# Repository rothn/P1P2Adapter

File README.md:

# Interface PCB for HomeBus®-based Devices

Ever wonder what A/C systems talk about? Have a HomeBus®-based system like P1P2? Satisfy your curiosity and reward yourself with a fun and challenging project! Build or send away for one of these from your favorite PCB manufacturer, and enjoy direct access to your system. The possibilities are vast!

## Key Features
- Read from and optionally write to your HomeBus® (i.e., the stream of data running between parts of your A/C system and/or other HomeBus®-based devices)
- Power an Arduino Uno and companion devices (e.g., ESP8266) directly from your pre-existing wiring (i.e., the two wires coming out of the wall and going into the thermostat) instead of spending time on complicated power management features for battery operation
- Enjoy fully-specified KiCad files and an MIT license, empowering you to tweak or integrate this design into your own projects

## Specs and Validation
Based on reference design from MAX22088 datasheet, which is optimized for 57.6kbps. Observed to operate correctly on a system running at 9600bps over multi-hour burn-in test.

# Usage

## Warning
Using this device may damage your HomeBus® system! Check with your doctor to see if Tinkering is right for you. In my experiments, I tested everything the best that I could before using it and I suggest that you do the same. Also, note that this involves connection to AC wiring (the HomeBus®). Be careful with that step, as it can be dangerous.

## PCB Creation / Sourcing

### PCB Manufacturer
As of 2021, I paid $5 for 5 boards plus $15 for shipping from PCBWay, and at least one tested OK.

1. Export gerber files from KiCad and send them to your PCB manufacturer. Most have specific requirements for options in the export process. For PCBWay, find these [here](https://www.pcbway.com/blog/help_center/Generate_Gerber_file_from_Kicad_5_1_6.html).
2. Upload the zip file and select the correct tolerances on your PCB manufacturer's website. See the "design rules" menu in KiCad for these. Be sure to run a design rules check in the PCB editor just to double-check that you have the right options. Also be sure to select the correct number of vias, etc. The automated system is likely to catch errors, but getting things wrong here might slow down the process and affect your quoted price.
3. For anything not in the design rules, I highly recommend selecting the cheapest option.

Note: Most manufacturers can also populate the board with components, but this will be an extra cost. DIY'ing it can be fun and cheaper with the proper tools (hot air tool, soldering iron with small tip). Your manufacturer of choice will likely have this option on their website.

### At-Home (Guidelines)
There are people who are experts at this. Refer to their advice (Google around). Take the suggestions below with a grain of salt, but above all else, please keep in mind the inherent danger of working with chemicals at home:

The PCB can be manufactured with an at-home process by printing onto high-quality acetate compatible with your printer, UV exposure onto a presensitized, double-sided PCB, development, and etching. Toner transfer is unlikely to work due to the tolerances involved. CNC milling is also an option.

## Connection to Arduino Uno

### Software
I recommend the [P1P2Serial](https://github.com/Arnold-n/P1P2Serial) Arduino-compatible C++ library to interact with the HomeBus®. The included P1P2Serial library is a great interface tool. The P1P2 monitor example may be a helpful starting point for its ability to dump out packets from the bus as raw hex to the Arduino's USB serial device. Keep in mind that the decoding logic may not make sense for your specific device.

### Hardware
My test configuration is as follows. To allow writing to the bus, drive the RST pin on the interface board to GND instead of +5V.

- Connect J2 to Positive (sometimes called P1) and J3 to Neutral (sometimes called P2) on the HomeBus®. These are likely interchangeable, but I have not validated this in practice. See termination section of schematic (bottom-left).
- +12V -> Arduino Vin
- +5V -> 1k resistor -> interface board RST (this disables output, move input to GND to enable)
- GND -> Arduino GND
- VLOGIC -> Arduino +5V
- DOUT -> Arduino8* ||** (20kOhm resistor -> Arduino GND)
- DIN -> NC***

\*: Arduino labeled input "8" in "Digital PWM" section (Port B, Input 0 of ATmega328p)\
\*\*: Shorthand notation for "in parallel with"\
\*\*\*: Shorthand for "no connect" -- the data input is not connected to anything since writing to the bus is disabled

Notes (__Important__)
- The maximum load on +12V is 200mA, per the MAX22088 spec
- Do not use +5V for anything that draws more than 70 milliamps, and do not use it at all for external loads if using +12V
- I have found +12V outputs a very noisy 12V DC in my particular application, but the spec says that 7.3V is typical, without listing a maximum.

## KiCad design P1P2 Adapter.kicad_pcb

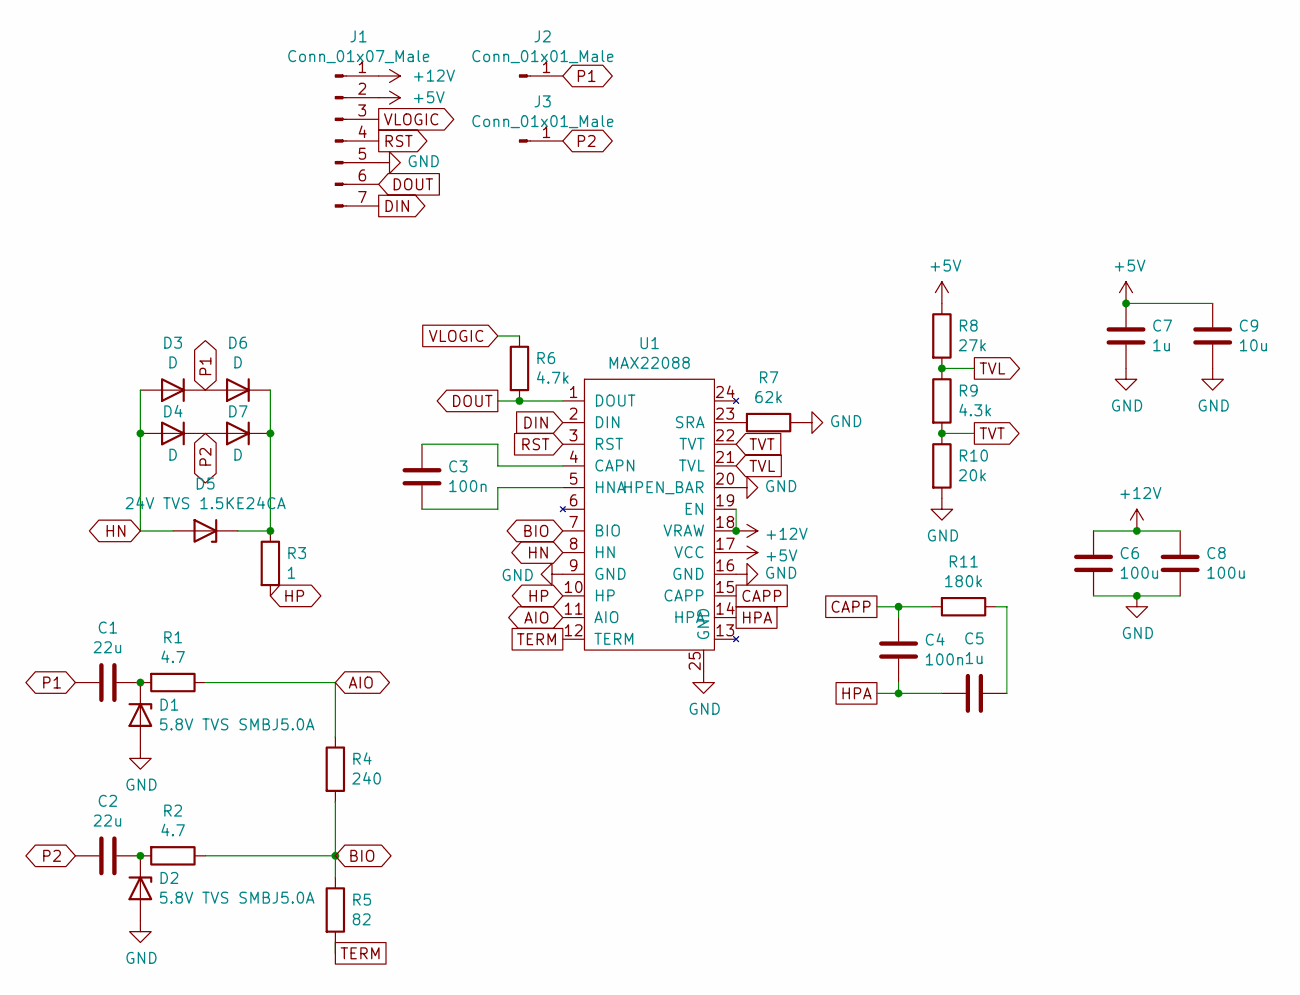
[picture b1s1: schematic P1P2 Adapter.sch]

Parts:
C1, C2: 22u; C_1206_3216Metric_Pad1.33x1.80mm_HandSolder
C3, C4: 100n; C_1206_3216Metric_Pad1.33x1.80mm_HandSolder
C5, C7: 1u; C_1206_3216Metric_Pad1.33x1.80mm_HandSolder
C6, C8: 100u; C_1206_3216Metric_Pad1.33x1.80mm_HandSolder
C9: 10u; C_1206_3216Metric_Pad1.33x1.80mm_HandSolder
D1, D2: 5.8V TVS SMBJ5.0A; D_SMB_Handsoldering
D3, D4, D6, D7: D; D_P600_R-6_P12.70mm_Horizontal
D5: 24V TVS 1.5KE24CA; D_DO-201_P12.70mm_Horizontal
J1: Conn_01x07_Male; PinHeader_1x07_P2.54mm_Vertical
J2, J3: Conn_01x01_Male; PinHeader_1x01_P2.54mm_Vertical
R1, R2: 4.7; R_1206_3216Metric_Pad1.30x1.75mm_HandSolder
R3: 1; R_1206_3216Metric_Pad1.30x1.75mm_HandSolder
R4: 240; R_1206_3216Metric_Pad1.30x1.75mm_HandSolder
R5: 82; R_1206_3216Metric_Pad1.30x1.75mm_HandSolder
R6: 4.7k; R_1206_3216Metric_Pad1.30x1.75mm_HandSolder
R7: 62k; R_1206_3216Metric_Pad1.30x1.75mm_HandSolder
R8: 27k; R_1206_3216Metric_Pad1.30x1.75mm_HandSolder
R9: 4.3k; R_1206_3216Metric_Pad1.30x1.75mm_HandSolder
R10: 20k; R_1206_3216Metric_Pad1.30x1.75mm_HandSolder
R11: 180k; R_1206_3216Metric_Pad1.30x1.75mm_HandSolder
U1: MAX22088; TQFN-24-1EP_4x4mm_P0.5mm_EP2.8x2.8mm_PullBack

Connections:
+5V: C7.1, C9.1, J1.2, R8.1, U1.17 (VCC)
+12V: C6.1, C8.1, J1.1, U1.18 (VRAW), U1.19 (EN)
AIO: R1.1, R4.1, U1.11 (AIO)
BIO: R2.1, R4.2, R5.1, U1.7 (BIO)
CAPP: C4.1, R11.2, U1.15 (CAPP)
DIN: J1.7, U1.2 (DIN)
DOUT: J1.6, R6.2, U1.1 (DOUT)
GND: C6.2, C7.2, C8.2, C9.2, D1.2 (A), D2.2 (A), J1.5, R7.1, R10.2, U1.9 (GND), U1.16 (GND), U1.20 (HPEN_BAR), U1.25 (GND)
HN: D3.2 (A), D4.2 (A), D5.2 (A), U1.8 (HN)
HP: R3.2, U1.10 (HP)
HPA: C4.2, C5.2, U1.14 (HPA)
unnamed: C1.2, D1.1 (K), R1.2
unnamed: C2.2, D2.1 (K), R2.2
unnamed: C3.1, U1.4 (CAPN)
unnamed: C3.2, U1.5 (HNA)
unnamed: C5.1, R11.1
unnamed: D5.1 (K), D6.1 (K), D7.1 (K), R3.1
unnamed: R7.2, U1.23 (SRA)
P1: C1.1, D3.1 (K), D6.2 (A), J2.1
P2: C2.1, D4.1 (K), D7.2 (A), J3.1
RST: J1.4, U1.3 (RST)
TERM: R5.2, U1.12 (TERM)
TVL: R8.2, R9.1, U1.21 (TVL)
TVT: R9.2, R10.1, U1.22 (TVT)
VLOGIC: J1.3, R6.1

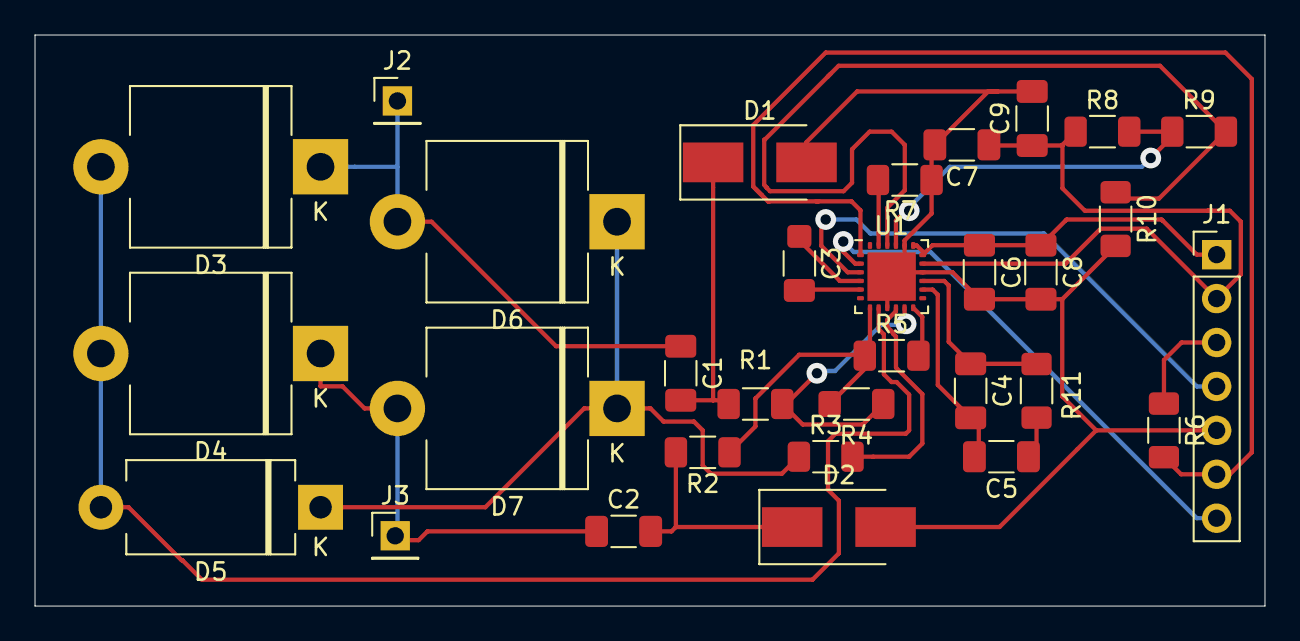
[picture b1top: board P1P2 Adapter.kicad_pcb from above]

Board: 2 copper layers, 71.1 x 33.0 mm, 31 parts (0 on the bottom side), 25 nets.

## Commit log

2021-09-15 Updated ground plane and PCB design
2021-11-28 Final touches, incl. design rule checks before having the board manufactured
2021-11-30 Fixed incorrect trim resistors and termination resistors. Credit goes to Arnold N, creator of P1P2Serial
2021-12-02 Made changes for 9600bps operation
2025-05-24 Fixed newline parsing
2025-06-14 Created using Colab
